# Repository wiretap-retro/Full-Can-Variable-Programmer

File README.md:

# Full Can Variable Programmer
A programmer for the full can variable oscillator.

## Info
Program the ATTiny85 and slip J1 over my other full can variable oscillator project, solder it, then control frequency with A & B. Please reference the Vogons thread on this with some excellent work by feipoa. https://www.vogons.org/viewtopic.php?t=82731 \
\
To be used with this project: https://github.com/wiretap-retro/Full-Can-Variable-Crystal-Oscillator/

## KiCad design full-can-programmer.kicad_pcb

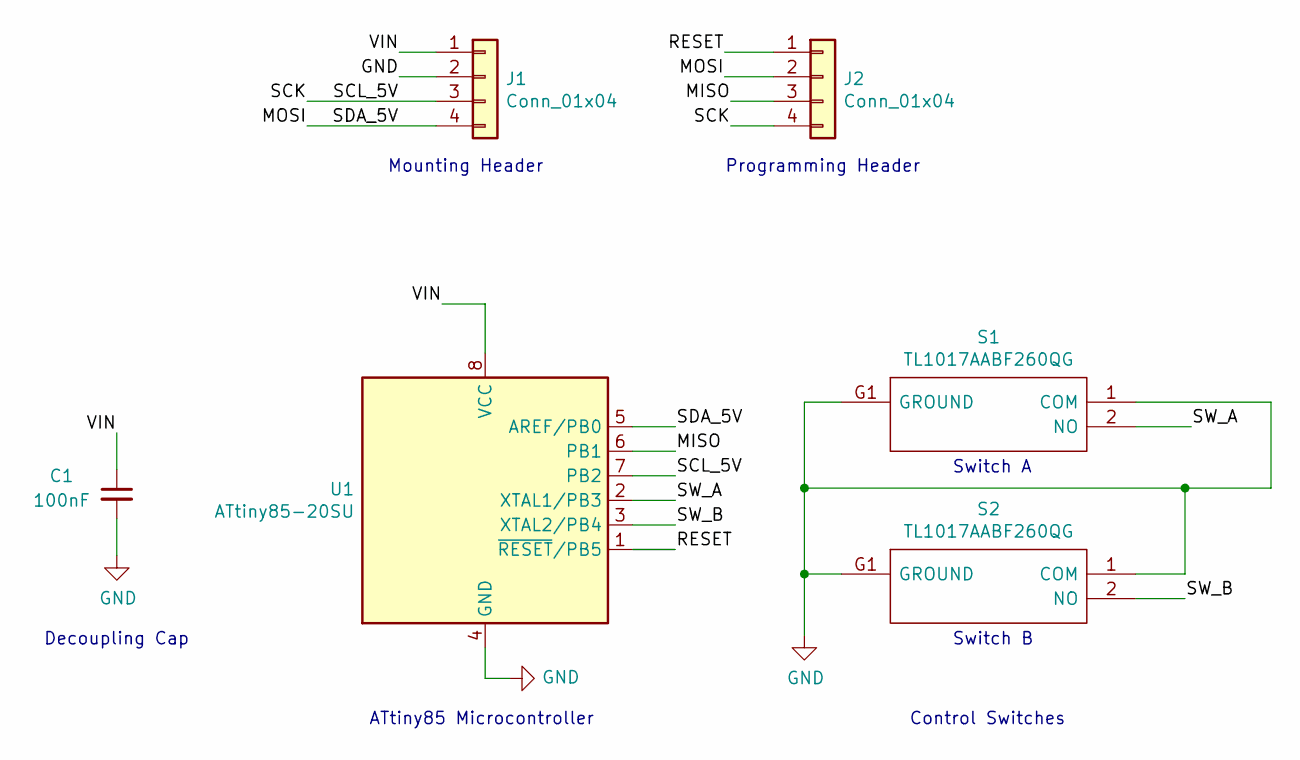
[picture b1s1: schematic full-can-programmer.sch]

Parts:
C1: 100nF; C_0805_2012Metric_Pad1.15x1.40mm_HandSolder
J1, J2: Conn_01x04; PinHeader_1x04_P2.54mm_Vertical
S1, S2: TL1017AABF260QG; Mouser Part Number 612-TL1017AABF260QG
U1: ATtiny85-20SU; SOIJ-8_5.3x5.3mm_P1.27mm

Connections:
/MISO: J2.3, U1.6 (PB1)
/MOSI: J1.4, J2.2, U1.5 (AREF/PB0)
/RESET: J2.1, U1.1 (~RESET~/PB5)
/SCK: J1.3, J2.4, U1.7 (PB2)
/SW_A: S1.2 (NO), U1.2 (XTAL1/PB3)
/SW_B: S2.2 (NO), U1.3 (XTAL2/PB4)
/VIN: C1.1, J1.1, U1.8 (VCC)
GND: C1.2, J1.2, S1.1 (COM), S1.G1 (GROUND), S2.1 (COM), S2.G1 (GROUND), U1.4 (GND)

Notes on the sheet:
Mounting Header
Decoupling Cap
ATtiny85 Microcontroller
Control Switches
Switch A
Switch B
Programming Header

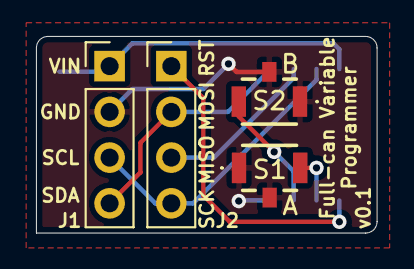
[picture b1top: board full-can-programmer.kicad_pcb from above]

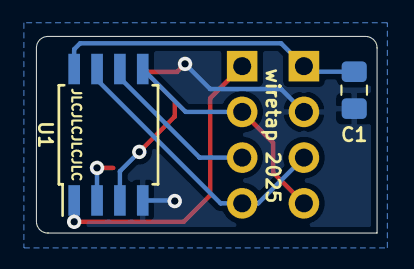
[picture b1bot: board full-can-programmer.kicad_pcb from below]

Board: 2 copper layers, 18.9 x 10.9 mm, 6 parts (2 on the bottom side), 8 nets.

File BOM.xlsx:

Reference | Quantity | Value | Footprint | Manufacturer | Part Number | Mouser Part Number | Notes
C1 | 1 | 100nF | Capacitor_SMD:C_0805_2012Metric_Pad1.15x1.40mm_HandSolder | Kyocera AVX | 08055C104K4Z4A | 581-08055C104K4Z4A | Any 0805 Ceramic 100nF Capacitor
J1, J2 | 2 | Conn_01x04 | Connector_PinHeader_2.54mm:PinHeader_1x04_P2.54mm_Vertical | Amphenol FCI | 68000-204HLF | 649-68000-204HLF | Only J2 needs to be populated
S1, S2 | 2 | TL1017AABF260QG | TL1017AABF260QG | E-Switch | TL1017AABF260QG | 612-TL1017AABF260QG | Tactile Buttons
U1 | 1 | ATtiny85-20SU | Package_SO:SOIJ-8_5.3x5.3mm_P1.27mm | Microchip | ATtiny85-20SU | 556-ATTINY85-20SU | Microcontroller
